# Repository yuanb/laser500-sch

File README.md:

# laser500-sch
Recreate the Laser 500 schematics in KiCAD, staying as close as possible to the diagrams in the original technical manual.

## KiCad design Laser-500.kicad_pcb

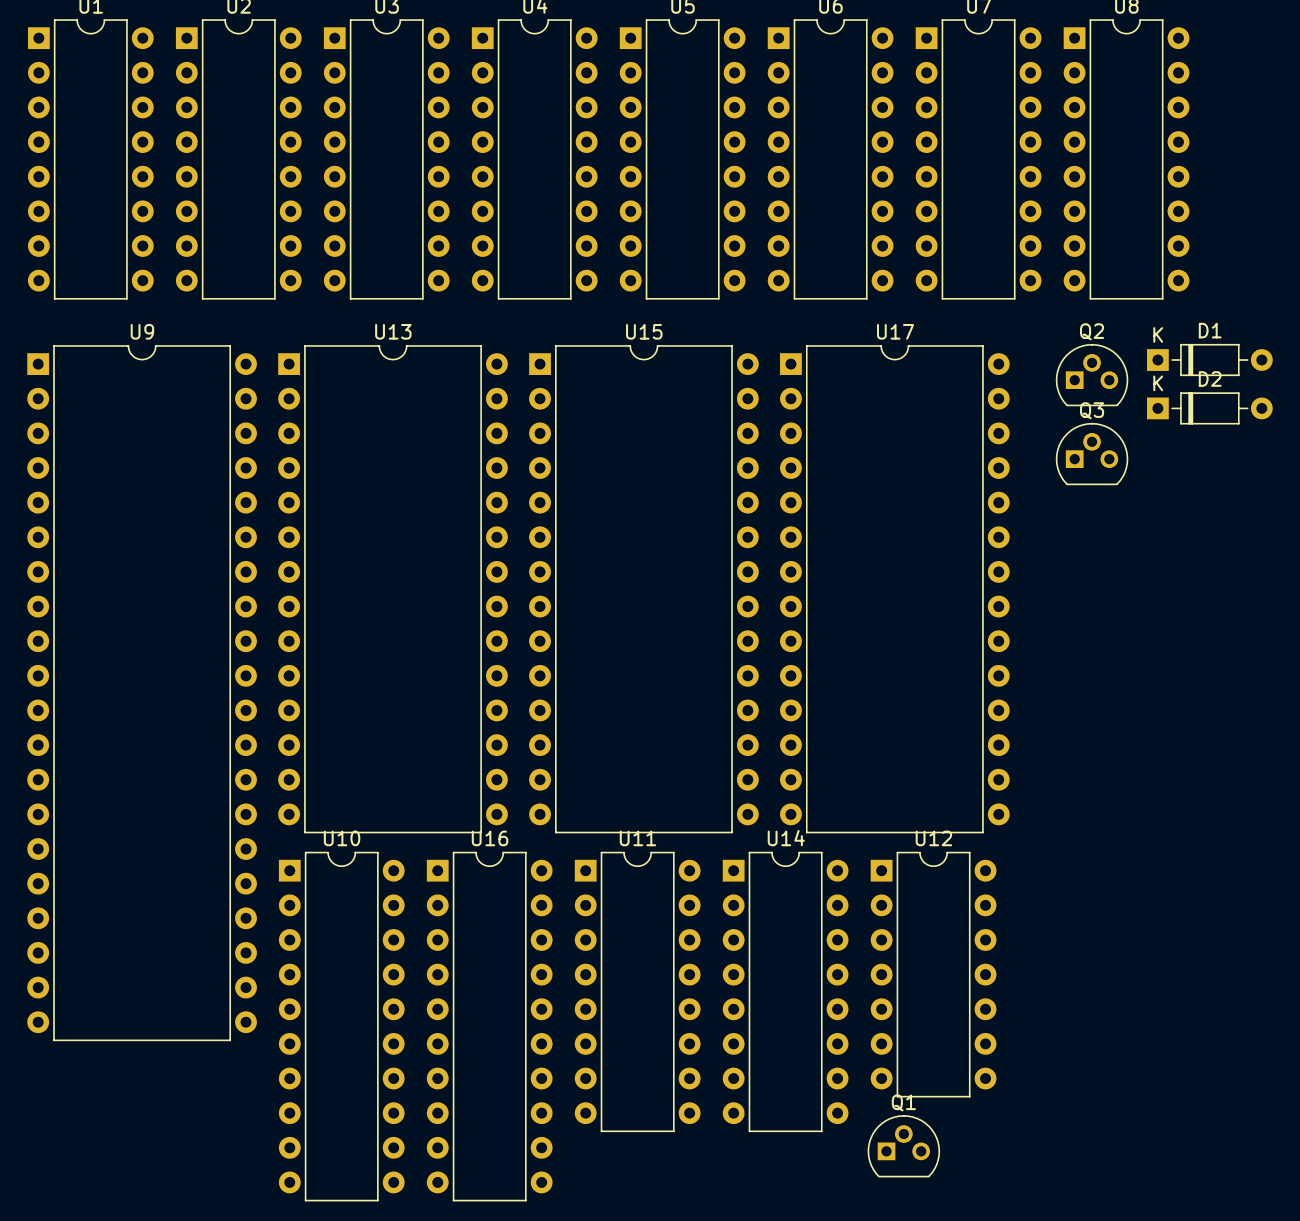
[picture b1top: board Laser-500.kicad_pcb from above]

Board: 2 copper layers, 22 parts (0 on the bottom side), 21 nets, no tracks yet.

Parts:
D1, D2: 1N4150; D_DO-35_SOD27_P7.62mm_Horizontal
Q1: 9018G; TO-92
Q2, Q3: 1402D; TO-92
U1, U2, U3, U4, U5, U6, U7, U8: TMM4164AP-15; DIP-16_W7.62mm
U9: Z80CPU; DIP-40_W15.24mm
U10: 74LS244; DIP-20_W7.62mm
U11, U14: 74LS257; DIP-16_W7.62mm
U12: 74LS00; DIP-14_W7.62mm
U13, U15: 27128; DIP-28_W15.24mm
U16: 74LS273; DIP-20_W7.62mm
U17: 2764; DIP-28_W15.24mm

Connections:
+5V: U1.8 (VCC), U2.8 (VCC), U3.8 (VCC), U4.8 (VCC), U5.8 (VCC), U6.8 (VCC), U7.8 (VCC), U8.8 (VCC)
<NO NET>: U1.16 (VSS), U2.16 (VSS), U3.16 (VSS), U4.16 (VSS), U5.16 (VSS), U6.16 (VSS), U7.16 (VSS), U8.16 (VSS)
MA0: U1.5 (A0), U2.5 (A0), U3.5 (A0), U4.5 (A0), U5.5 (A0), U6.5 (A0), U7.5 (A0), U8.5 (A0)
MA1: U1.7 (A1), U2.7 (A1), U3.7 (A1), U4.7 (A1), U5.7 (A1), U6.7 (A1), U7.7 (A1), U8.7 (A1)
MA2: U1.6 (A2), U2.6 (A2), U3.6 (A2), U4.6 (A2), U5.6 (A2), U6.6 (A2), U7.6 (A2), U8.6 (A2)
MA3: U1.12 (A3), U2.12 (A3), U3.12 (A3), U4.12 (A3), U5.12 (A3), U6.12 (A3), U7.12 (A3), U8.12 (A3)
MA4: U1.11 (A4), U2.11 (A4), U3.11 (A4), U4.11 (A4), U5.11 (A4), U6.11 (A4), U7.11 (A4), U8.11 (A4)
MA5: U1.10 (A5), U2.10 (A5), U3.10 (A5), U4.10 (A5), U5.10 (A5), U6.10 (A5), U7.10 (A5), U8.10 (A5)
MA6: U1.13 (A6), U2.13 (A6), U3.13 (A6), U4.13 (A6), U5.13 (A6), U6.13 (A6), U7.13 (A6), U8.13 (A6)
MA7: U1.9 (A7), U2.9 (A7), U3.9 (A7), U4.9 (A7), U5.9 (A7), U6.9 (A7), U7.9 (A7), U8.9 (A7)
RD0: U1.2 (Din), U1.14 (Dout)
RD1: U2.2 (Din), U2.14 (Dout)
RD2: U3.2 (Din), U3.14 (Dout)
RD3: U4.2 (Din), U4.14 (Dout)
RD4: U5.2 (Din), U5.14 (Dout)
RD5: U6.2 (Din), U6.14 (Dout)
RD6: U7.2 (Din), U7.14 (Dout)
RD7: U8.2 (Din), U8.14 (Dout)
~CAS: U1.15 (~CAS), U2.15 (~CAS), U3.15 (~CAS), U4.15 (~CAS), U5.15 (~CAS), U6.15 (~CAS), U7.15 (~CAS), U8.15 (~CAS)
~RAMW: U1.3 (W), U2.3 (W), U3.3 (W), U4.3 (W), U5.3 (W), U6.3 (W), U7.3 (W), U8.3 (W)
~RAS: U1.4 (~RAS), U2.4 (~RAS), U3.4 (~RAS), U4.4 (~RAS), U5.4 (~RAS), U6.4 (~RAS), U7.4 (~RAS), U8.4 (~RAS)

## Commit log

2024-12-16 Initial push
2024-12-16 RAM4164
2024-12-19 First Draft - RAM
2024-12-19 Started video_cassette sch
2024-12-20 Finished Y-signal generation
2024-12-24 Updated symbols
    74LS257
    GA1
2024-12-24 More Laser 500 symbols
2024-12-27 A few Boxing day updates
    1. Add Laser 500 Mainboard PCB photo
    2. Updated Main circuit ICs and their symbols.
    3. Updated references according to PCB photo
2025-01-03 Started A[0..15] and MA[0..7] on main circuit
2025-01-03 Main circuit : Finished most of the buses
2025-01-06 End of vacation
2025-01-09 More updates on Top and Main diagrams
2025-04-27 Exported main circuit
2025-10-20 Upgraded to KiCad 9.0.5
